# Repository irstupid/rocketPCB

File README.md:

# rocketPCB
my submission to the hackclub solder thing
hi, im ian. i made a little rocket ship keychain, and when you press the button it will slowly charge up using capacitors. it uses 3 capacitors, wich is more than is allowed, but i have my own capacitors that i intend to use. so with that, the bill of components is:
3x 220Ω resisitors
3x 4.7kΩ resistors
3x 5mm LED (preferebly red, yellow, and green :))
3x NPN transistors
1x battery holder
capacitors are already supplied

this is the view of the schematic:

this is the view of the PCB routes and stuff:

this is the view of the 3D moddle:

this is the view of the back:

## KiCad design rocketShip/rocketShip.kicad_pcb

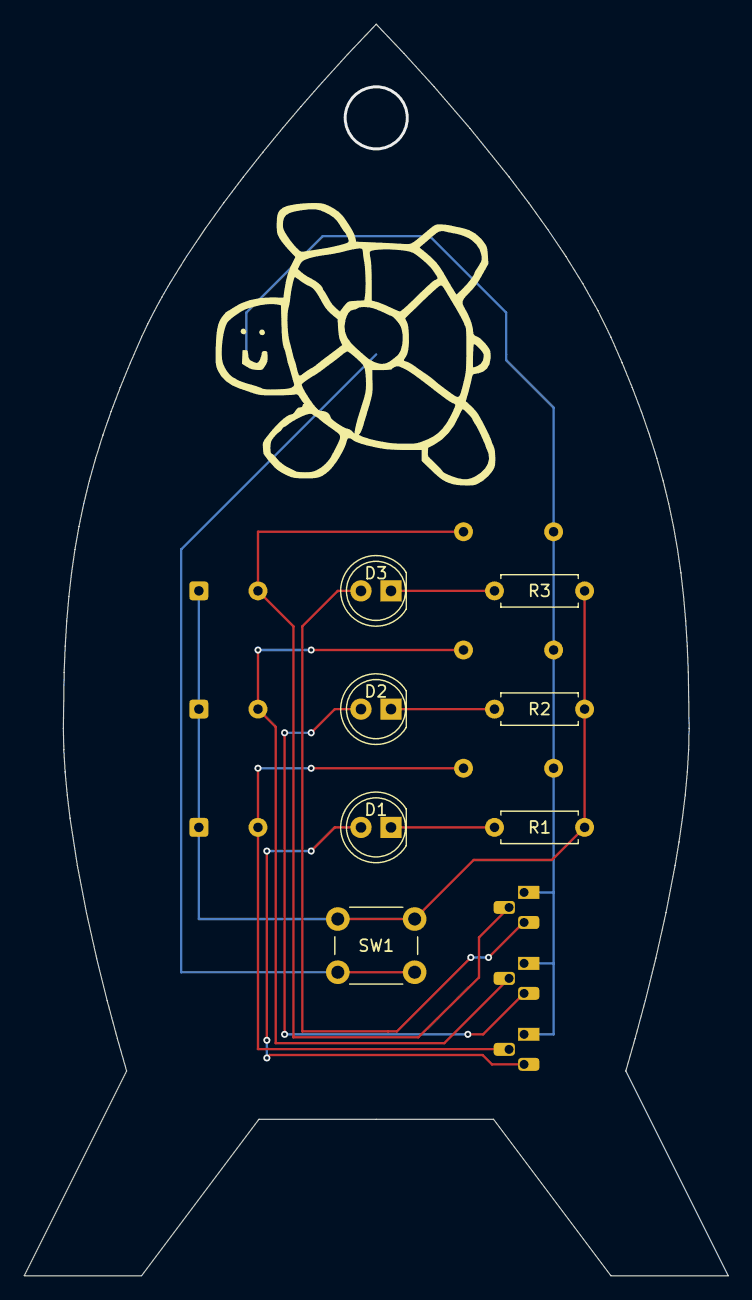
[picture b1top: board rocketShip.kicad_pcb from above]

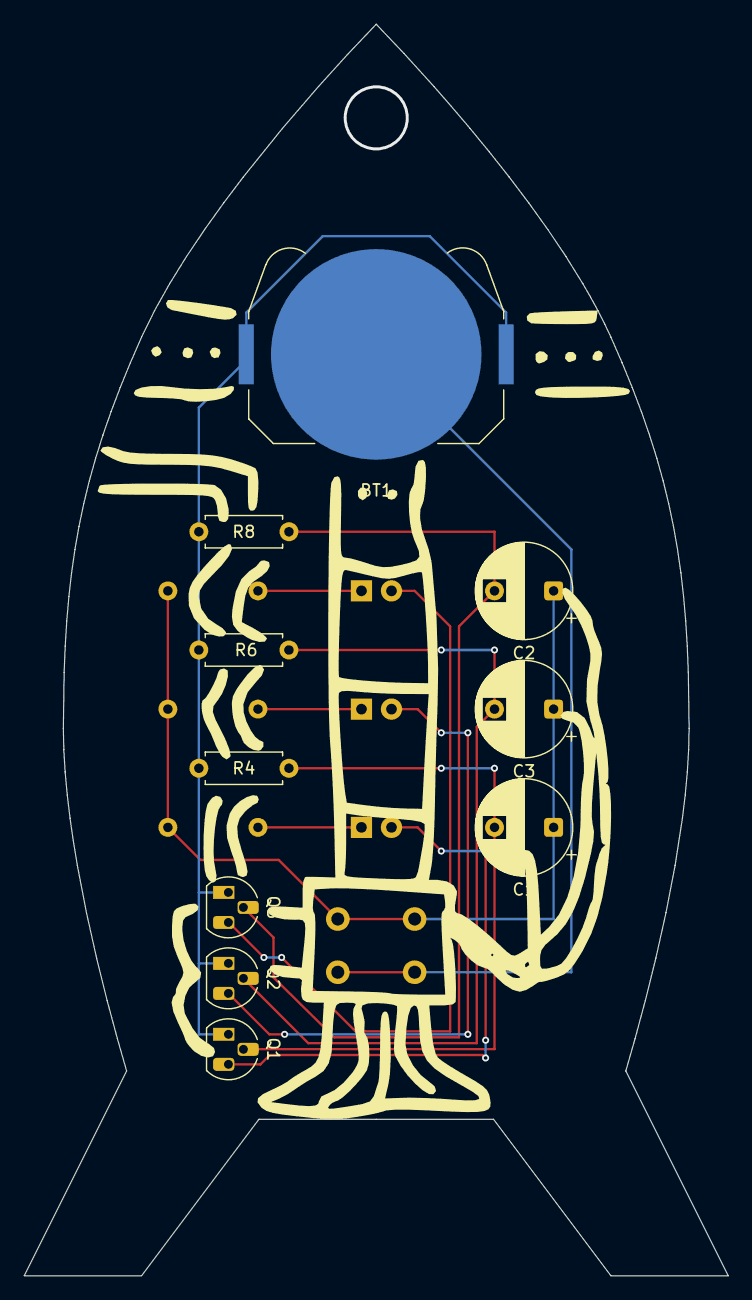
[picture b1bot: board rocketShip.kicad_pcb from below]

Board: 2 copper layers, 59.5 x 105.8 mm, 17 parts (10 on the bottom side), 12 nets.

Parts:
BT1: Battery_Cell; BatteryHolder_Keystone_3034_1x20mm
C1, C2, C3: C; CP_Radial_D8.0mm_P5.00mm
D1, D2, D3: LED; LED_D5.0mm
Q1, Q2, Q3: NPN; TO-92L_HandSolder
R1, R2, R3, R4, R6, R8: R; R_Axial_DIN0207_L6.3mm_D2.5mm_P7.62mm_Horizontal
SW1: SW_Push; SW_PUSH_6mm

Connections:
unnamed: BT1.1 (+), Q1.1 (C), Q2.1 (C), Q3.1 (C), R4.1, R6.1, R8.1
unnamed: BT1.2 (-), SW1.2
unnamed: C1.1, C2.1, C3.1, R1.2, R2.2, R3.2, SW1.1
unnamed: D1.2 (A), Q1.3 (E)
unnamed: D1.1 (K), R1.1
unnamed: D2.2 (A), Q2.3 (E)
unnamed: D2.1 (K), R2.1
unnamed: D3.2 (A), Q3.3 (E)
unnamed: D3.1 (K), R3.1
unnamed: C1.2, Q1.2 (B), R4.2
unnamed: C3.2, Q2.2 (B), R6.2
unnamed: C2.2, Q3.2 (B), R8.2

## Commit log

2025-05-23 moving all the things into this repo
2025-05-23 it would be pretty cool if this worked
2025-05-23 it did :)
2025-05-23 done?
2025-05-23 added some back art
2025-05-23 remember to update your readmes
2025-05-23 preferably correctly
2025-05-29 sumble fumble
